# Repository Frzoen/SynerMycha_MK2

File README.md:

# SynerMycha Mk II
Repozytorium dla projektu robota micromouse

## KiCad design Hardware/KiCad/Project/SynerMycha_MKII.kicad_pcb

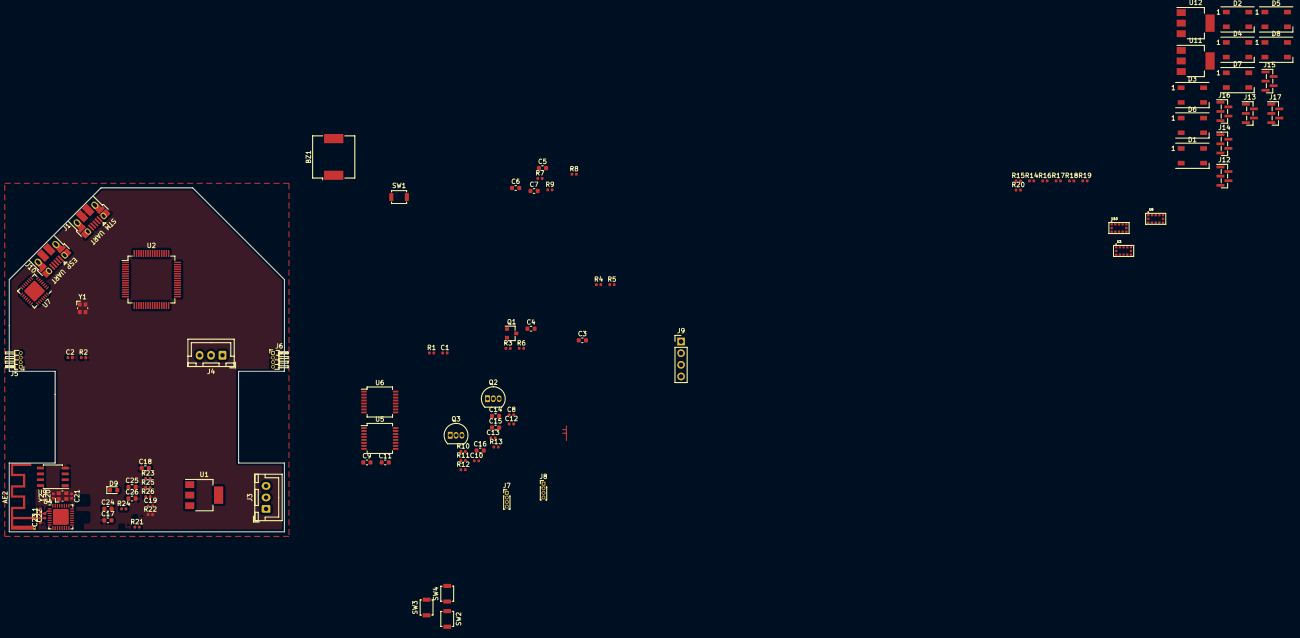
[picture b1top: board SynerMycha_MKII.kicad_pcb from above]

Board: 4 copper layers, 60.0 x 75.0 mm, 100 parts (0 on the bottom side), 87 nets.

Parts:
AE2: 2.4GHz; Texas_SWRA117D_2.4GHz_Right
BZ1: Buzzer; Buzzer_CUI_CPT-9019S-SMT
C1, C2: 8pF; C_0402_1005Metric
C3, C4, C5, C6, C7: 2.2uF; C_0603_1608Metric
C8, C10, C12, C13: 0.1uF; C_0402_1005Metric
C9, C11, C14, C16, C17, C18: 10uF; C_0603_1608Metric
C15, C24, C25, C26: 0.1uF; C_0603_1608Metric
C19: 1uF; C_0402_1005Metric
C20, C21: 5.6pF; C_0402_1005Metric
C22: 8.6pF; C_0402_1005Metric
C23: 2.4pF; C_0402_1005Metric
D1, D2, D3, D4, D5, D6, D7, D8: WS2812B; LED_WS2812B_PLCC4_5.0x5.0mm_P3.2mm
D9: BLUE; LED_0603_1608Metric
J1, J10: USB_B_Micro; USB_Micro-B_Amphenol_10103594-0001LF_Horizontal
J3, J4: B3B-XH-A; JST_XH_B3B-XH-A_1x03_P2.50mm_Vertical
J5, J6: Conn_01x04; PinHeader_1x04_P1.00mm_Horizontal
J7, J8: Conn_01x04; PinHeader_1x04_P1.00mm_Vertical
J9: Conn_01x04; PinHeader_1x04_P2.54mm_Vertical
J12, J13, J14, J15, J16, J17: Conn_01x05; PinHeader_1x05_P1.00mm_Vertical_SMD_Pin1Left
L1: 1.5nH; L_0402_1005Metric
Q1: IRLML9301TRPBF; SOT-23
Q2, Q3: S8050; TO-92_Inline
R1, R2: calculate; R_0402_1005Metric
R3, R4, R7, R8, R9, R10, R11, R14, R15, R16: 10k; R_0402_1005Metric
R5, R17, R19: 2K2; R_0402_1005Metric
R6, R18, R20: 8K2; R_0402_1005Metric
R12, R13: 12k; R_0402_1005Metric
R21, R22, R23, R24, R25, R26: 12K; R_0402_1005Metric
SW1, SW2, SW3, SW4: SW_Push; SW_SPST_B3U-1000P
U1, U11, U12: LM317_3PinPackage; SOT-223
U2: STM32F446RETx; LQFP-64_10x10mm_P0.5mm
U3, U8, U10: VL53L0X; SENSOR_VL53L0X
U4: ESP8266EX; QFN-32-1EP_5x5mm_P0.5mm_EP3.45x3.45mm
U5, U6: AS5045B; SSOP-16_5.3x6.2mm_P0.65mm
U7: CP2102N-A01-GQFN28; QFN-28-1EP_5x5mm_P0.5mm_EP3.35x3.35mm
U9: ESP-PSRAM32; SOIC-8_3.9x4.9mm_P1.27mm
Y1: 16Mhz, 8pF; Crystal_SMD_Abracon_ABM10-4Pin_2.5x2.0mm
Y2: 26Mhz, 5.6pF; Crystal_SMD_Abracon_ABM10-4Pin_2.5x2.0mm

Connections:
+2V8: R19.1, U12.2
+3V3: C12.2, C15.2, C16.2, C24.1, C25.1, C26.1, D1.1, D2.1, D3.1, D4.1, D5.1, D6.1, D7.1, D8.1, J5.4, J6.1, J9.3, R3.1, R7.1, R8.1, R9.1, R17.1, R21.1, R22.1, R23.1, R24.1, U2.1, U2.13, U2.19, U2.32, U2.48, U2.64, U4.1, U4.3, U4.4, U4.11, U4.17, U4.29, U4.30, U7.6, U7.7, U9.8, U11.2
+6V: R5.1, U1.2
/BATT_MEAS: R1.2, R2.1, U2.11
/BOOT0: R4.1, U2.60
/ENC_WHEEL_L_A: J5.1, U2.22
/ENC_WHEEL_L_B: J5.2, U2.23
/ENC_WHEEL_R_A: J6.4, U2.59
/ENC_WHEEL_R_B: J6.3, U2.58
/ESP_D+: J10.3, U7.4
/ESP_D-: J10.2, U7.5
/ESP_EN: R24.2, U4.7
/ESP_GPIO0: Q2.2, R12.1, R23.2, U4.15
/ESP_GPIO2: D9.1, U4.14
/ESP_RX: U4.25, U7.26
/ESP_TX: U4.26, U7.25
/ESP_VBUS: C13.2, C14.2, J10.1, U7.8
/ESP_~RESET: C19.1, Q3.2, R13.1, R21.2, U4.32
/LCD_IMU_SCL: J9.2, U2.41
/LCD_IMU_SDA: J9.1, U2.40
/NRST: C3.1, R3.2, SW1.2, U2.7
/OSC_IN: C1.1, U2.5, Y1.3
/OSC_OUT: C2.1, U2.6, Y1.1
/STM_D+: J1.3, U2.45
/STM_D-: J1.2, U2.44
/VCAP_1: C4.1, U2.30
GND: AE2.2, C1.2, C2.2, C3.2, C4.2, C5.2, C6.2, C7.2, C12.1, C13.1, C14.1, C15.1, C16.1, C17.1, C18.1, C19.2, C20.2, C21.2, C23.1, C24.2, C25.2, C26.2, D1.3, D2.3, D3.3, D4.3, D5.3, D6.3, D7.3, D8.3, J1.5, J1.6, J5.3, J6.2, J9.4, J10.5, L1.2, Q1.1, R2.2, R4.2, R6.2, R18.2, R20.2, R25.1, R26.2, SW1.1, SW2.1, SW3.1, SW4.1, U2.12, U2.18, U2.31, U2.47, U2.63, U4.33, U7.3, U9.4, Y1.2, Y2.2
unnamed: AE2.1, C22.1, C23.2
unnamed: C5.1, R7.2, SW2.2
unnamed: C6.1, R8.2, SW3.2
unnamed: C7.1, R9.2, SW4.2
unnamed: C8.1, C9.1, J7.3, U5.7
unnamed: C8.2, C9.2, J7.4, R10.1, U5.15, U5.16
unnamed: C10.1, C11.1, J8.3, U6.7
unnamed: C10.2, C11.2, J8.4, R11.1, U6.15, U6.16
unnamed: C20.1, U4.27, Y2.3
unnamed: C21.1, U4.28, Y2.1
unnamed: C22.2, L1.1, U4.2
unnamed: D1.2, D2.4
unnamed: D2.2, D3.4
unnamed: D3.2, D4.4
unnamed: D4.2, D5.4
unnamed: D5.2, D6.4
unnamed: D6.2, D7.4
unnamed: D7.2, D8.4
unnamed: D9.2, R22.2
unnamed: J3.1, J4.1
unnamed: J3.2, J4.2
unnamed: J3.3, J4.3
unnamed: J7.1, U5.3
unnamed: J7.2, U5.4
unnamed: J8.1, U6.3
unnamed: J8.2, U6.4
unnamed: J13.1, R14.1, U3.1, U3.11
unnamed: J13.2, U3.2, U3.3, U3.4, U3.6, U3.12
unnamed: J13.3, U3.9
unnamed: J13.4, U3.10
unnamed: J13.5, U3.5
unnamed: J15.1, R15.1, U8.1, U8.11
unnamed: J15.2, U8.2, U8.3, U8.4, U8.6, U8.12
unnamed: J15.3, U8.9
unnamed: J15.4, U8.10
unnamed: J15.5, U8.5
unnamed: J17.1, R16.1, U10.1, U10.11
unnamed: J17.2, U10.2, U10.3, U10.4, U10.6, U10.12
unnamed: J17.3, U10.9
unnamed: J17.4, U10.10
unnamed: J17.5, U10.5
unnamed: Q2.1, R13.2, U7.28
unnamed: Q3.1, R12.2, U7.24
unnamed: R5.2, R6.1, U1.1
unnamed: R10.2, U5.11
unnamed: R11.2, U6.11
unnamed: R14.2, U3.7
unnamed: R15.2, U8.7
unnamed: R16.2, U10.7
unnamed: R17.2, R18.1, U11.1
unnamed: R19.2, R20.1, U12.1
unnamed: R25.2, U4.13
unnamed: R26.1, U4.31
unnamed: U4.18, U9.7
unnamed: U4.19, U9.3
unnamed: U4.20, U9.1
unnamed: U4.21, U9.6
unnamed: U4.22, U9.2
unnamed: U4.23, U9.5
VCC: C17.2, C18.2, Q1.3, R1.1, U1.3, U11.3, U12.3

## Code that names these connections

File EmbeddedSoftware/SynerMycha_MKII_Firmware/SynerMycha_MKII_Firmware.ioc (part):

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Mcu.Name=STM32F446R(C-E)Tx
Mcu.Package=LQFP64
Mcu.UserName=STM32F446RETx
PA0-WKUP.GPIOParameters=GPIO_Label
PA0-WKUP.GPIO_Label=ENC_MOT_L_A
PA0-WKUP.Signal=S_TIM5_CH1
PA1.GPIOParameters=GPIO_Label
PA1.GPIO_Label=ENC_MOT_L_B
PA1.Signal=S_TIM5_CH2
PA11.Mode=Device_Only
PA11.Signal=USB_OTG_FS_DM
PA12.Mode=Device_Only
PA12.Signal=USB_OTG_FS_DP
PA13.GPIOParameters=GPIO_Label
PA13.GPIO_Label=JTSM
PA13.Mode=Serial_Wire
PA13.Signal=SYS_JTMS-SWDIO
PA14.GPIOParameters=GPIO_Label
PA14.GPIO_Label=JTCLK
PA14.Mode=Serial_Wire
PA14.Signal=SYS_JTCK-SWCLK
PA2.GPIOParameters=GPIO_Label
PA2.GPIO_Label=UART_TX
PA2.Mode=Asynchronous
PA2.Signal=USART2_TX
PA3.GPIOParameters=GPIO_Label
PA3.GPIO_Label=RUART_X
PA3.Mode=Asynchronous
PA3.Signal=USART2_RX
PA4.GPIOParameters=GPIO_Label
PA4.GPIO_Label=LED_1
PA4.Signal=GPIO_Output
PA5.GPIOParameters=GPIO_Label
PA5.GPIO_Label=ENC_MOT_R_A
PA5.Signal=S_TIM2_CH1_ETR
PA6.GPIOParameters=GPIO_Label
PA6.GPIO_Label=ENC_WHEEL_L_A
PA6.Signal=S_TIM3_CH1
PA7.GPIOParameters=GPIO_Label
PA7.GPIO_Label=ENC_WHEEL_L_B
PA7.Signal=S_TIM3_CH2
PA8.GPIOParameters=GPIO_Label
PA8.GPIO_Label=LCD_IMU_SCL
PA8.Mode=I2C
PA8.Signal=I2C3_SCL
PB0.GPIOParameters=GPIO_Label
PB0.GPIO_Label=LED_4
PB0.Signal=GPIO_Output
PB1.GPIOParameters=GPIO_Label
PB1.GPIO_Label=BUTTON_UP
PB1.Signal=GPIO_Input
PB10.GPIOParameters=GPIO_Label
PB10.GPIO_Label=BUTTON_OK
PB10.Signal=GPIO_Input
PB2.GPIOParameters=GPIO_Label
PB2.GPIO_Label=BUTTON_DOWN
PB2.Signal=GPIO_Input
PB3.GPIOParameters=GPIO_Label
PB3.GPIO_Label=ENC_MOT_R_B
PB3.Signal=S_TIM2_CH2
PB4.GPIOParameters=GPIO_Label
PB4.GPIO_Label=VL53_FL_XSHUT
PB4.Signal=GPIO_Output
PB5.GPIOParameters=GPIO_Label
PB5.GPIO_Label=VL53_L_XSHUT
PB5.Signal=GPIO_Output
PB6.GPIOParameters=GPIO_Label
PB6.GPIO_Label=ENC_WHEEL_R_B
PB6.Signal=S_TIM4_CH1
PB7.GPIOParameters=GPIO_Label
PB7.GPIO_Label=ENC_WHEEL_R_A
PB7.Signal=S_TIM4_CH2
PB8.GPIOParameters=GPIO_Label
PB8.GPIO_Label=VL53_SCL
PB8.Mode=I2C
PB8.Signal=I2C1_SCL
PB9.GPIOParameters=GPIO_Label
PB9.GPIO_Label=VL53_SDA
PB9.Mode=I2C
PB9.Signal=I2C1_SDA
PC0.GPIOParameters=GPIO_Label
PC0.GPIO_Label=MOT_R_A
PC0.Signal=GPIO_Output
PC1.GPIOParameters=GPIO_Label
PC1.GPIO_Label=MOT_NSTBY
PC1.Signal=GPIO_Output
PC11.GPIOParameters=GPIO_Label
PC11.GPIO_Label=VL53_R_XSHUT
PC11.Signal=GPIO_Output
PC12.GPIOParameters=GPIO_Label
PC12.GPIO_Label=VL53_FR_XSHUT
PC12.Signal=GPIO_Output
PC13.GPIOParameters=GPIO_Label
PC13.GPIO_Label=MOT_L_B
PC13.Signal=GPIO_Output
PC14-OSC32_IN.GPIOParameters=GPIO_Label
PC14-OSC32_IN.GPIO_Label=MOT_L_A
PC14-OSC32_IN.Signal=GPIO_Output
PC15-OSC32_OUT.GPIOParameters=GPIO_Label
PC15-OSC32_OUT.GPIO_Label=MOT_R_B
PC15-OSC32_OUT.Signal=GPIO_Output
PC3.GPIOParameters=GPIO_Label
PC3.GPIO_Label=BATT
PC3.Signal=ADCx_IN13
PC4.GPIOParameters=GPIO_Label
PC4.GPIO_Label=LED_2
PC4.Signal=GPIO_Output
PC5.GPIOParameters=GPIO_Label
PC5.GPIO_Label=LED_3
PC5.Signal=GPIO_Output
PC6.GPIOParameters=GPIO_Label
PC6.GPIO_Label=MOT_L_PWM
PC6.Signal=S_TIM8_CH1
PC7.GPIOParameters=GPIO_Label
PC7.GPIO_Label=MOT_R_PWM
PC7.Signal=S_TIM8_CH2
PC9.GPIOParameters=GPIO_Label
PC9.GPIO_Label=LDC_IMU_SDA
PC9.Mode=I2C
PC9.Signal=I2C3_SDA
PD2.GPIOParameters=GPIO_Label
PD2.GPIO_Label=VL53_F_XSHUT
PD2.Signal=GPIO_Output
PH0-OSC_IN.Mode=HSE-External-Oscillator
PH0-OSC_IN.Signal=RCC_OSC_IN
PH1-OSC_OUT.Mode=HSE-External-Oscillator
PH1-OSC_OUT.Signal=RCC_OSC_OUT
RCC.HSE_VALUE=16000000
RCC.SYSCLKFreq_VALUE=180000000
RCC.SYSCLKSource=RCC_SYSCLKSOURCE_PLLRCLK
board=custom

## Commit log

2020-01-31 Create basic dimmensions for robot, kicad project
2020-01-31 Gitignore for kicad
2020-01-31 Generate basic project with clock configuration in CubeMX
2020-02-02 Configuration of timers, basic concept of pinout
2020-02-25 Correction in gpio init
2020-02-25 Basic uC config, added power and bluetooth antenna
